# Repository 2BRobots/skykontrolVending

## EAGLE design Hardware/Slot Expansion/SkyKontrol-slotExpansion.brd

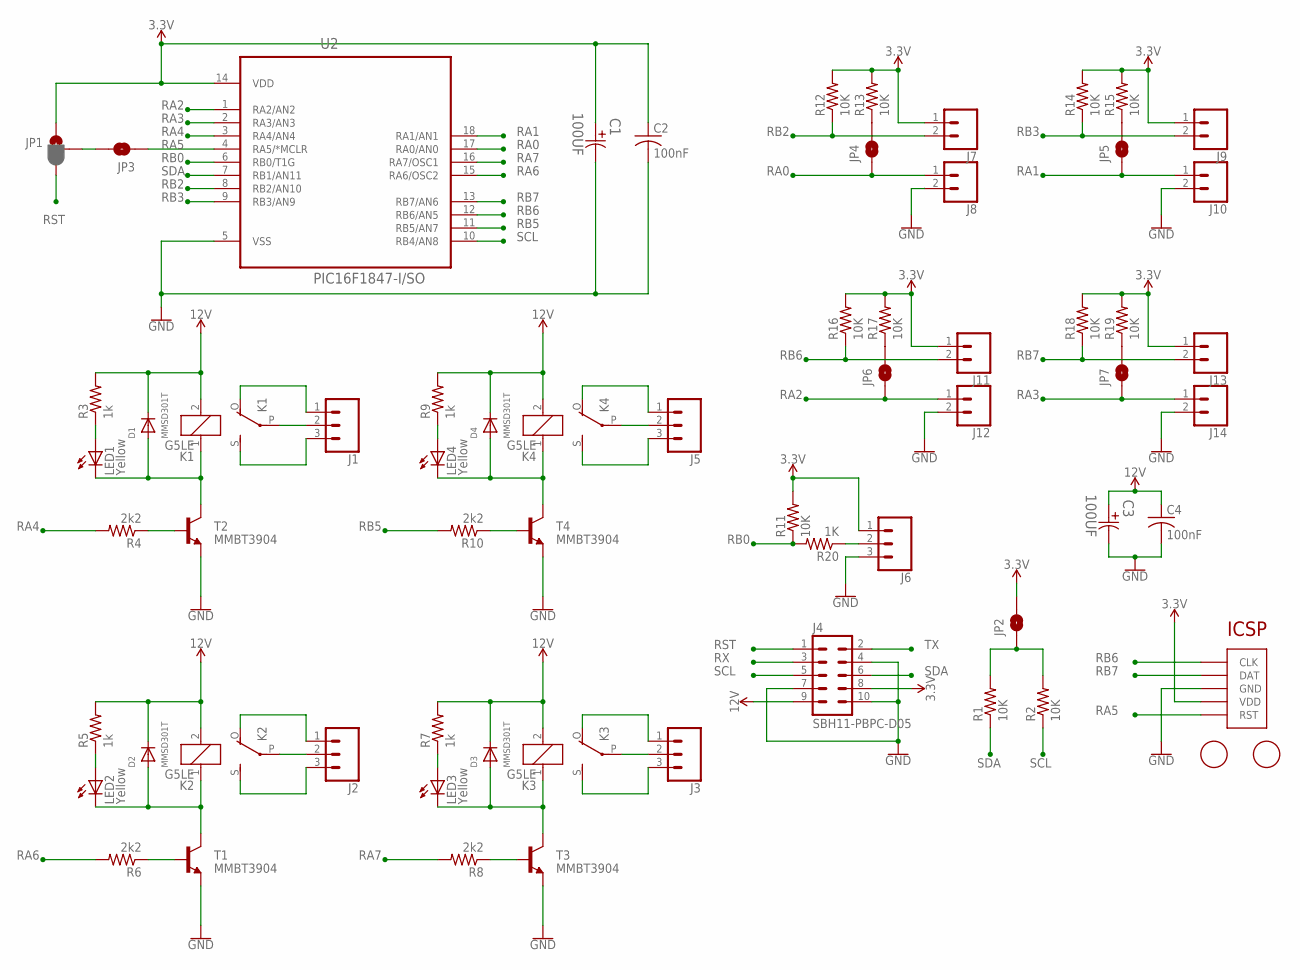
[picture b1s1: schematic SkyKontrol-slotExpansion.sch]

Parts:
C1, C3: 100UF; CAPAE660X800N
C2, C4: 100nF; C0603K
D1, D2, D3, D4: MMSD301T; SOD-123
J1, J2, J3, J5, J6: CONN_03-SCREW-5MM; SCREWTERMINAL-5MM-3
J4: SBH11-PBPC-D05
J7, J8, J9, J10, J11, J12, J13, J14: CONN_025MM; SCREWTERMINAL-5MM-2
JP1: JUMPER-SMT_3_1-NC_PASTE_SILK; SMT-JUMPER_3_1-NC_PASTE_SILK
JP2, JP3, JP4, JP5, JP6, JP7: JUMPER-SMT_2_NO_SILK; SMT-JUMPER_2_NO_SILK
K1, K2, K3, K4: G5LE
LED1, LED2, LED3, LED4: Yellow; CHIPLED_1206
R1, R2, R11, R12, R13, R14, R15, R16, R17, R18, R19: 10K; R0805
R3, R5, R7, R9: 1k; R0805
R4, R6, R8, R10: 2k2; R0805
R20: 1K; R0805
T1, T2, T3, T4: MMBT3904; SOT23-BEC
U2: PIC16F1847-I/SO; SOIC127P1030X265-18N
U$1, U$3: FIDUCIAL; FIDUCIAL_1MM
U$2: ICSP_POGO

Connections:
3.3V: C1.1, C2.1, J4.8, J6.1, J7.1, J9.1, J11.1, J13.1, JP1.1, JP2.2, R11.2, R12.2, R13.2, R14.2, R15.2, R16.2, R17.2, R18.2, R19.2, U2.14 (VDD), U$2.P$2 (VDD)
12V: C3.1, C4.1, D1.C, D2.C, D3.C, D4.C, J4.9, K1.2, K2.2, K3.2, K4.2, R3.2, R5.2, R7.2, R9.2
GND: C1.2, C2.2, C3.2, C4.2, J4.4, J4.7, J4.10, J6.3, J8.2, J10.2, J12.2, J14.2, T1.E, T2.E, T3.E, T4.E, U2.5 (VSS), U$2.P$3 (GND)
unnamed: JP1.2, JP3.2
unnamed: J1.2, K1.P
unnamed: J1.3, K1.S
unnamed: J1.1, K1.O
unnamed: JP2.1, R1.2, R2.2
unnamed: D1.A, K1.1, LED1.C, T2.C
unnamed: J2.2, K2.P
unnamed: J2.3, K2.S
unnamed: LED1.A, R3.1
unnamed: R4.1, T2.B
unnamed: J6.2, R20.1
unnamed: J2.1, K2.O
unnamed: D2.A, K2.1, LED2.C, T1.C
unnamed: LED2.A, R5.1
unnamed: R6.1, T1.B
unnamed: J3.2, K3.P
unnamed: J3.3, K3.S
unnamed: J3.1, K3.O
unnamed: D3.A, K3.1, LED3.C, T3.C
unnamed: LED3.A, R7.1
unnamed: R8.1, T3.B
unnamed: J5.2, K4.P
unnamed: J5.3, K4.S
unnamed: J5.1, K4.O
unnamed: D4.A, K4.1, LED4.C, T4.C
unnamed: LED4.A, R9.1
unnamed: R10.1, T4.B
unnamed: JP4.2, R13.1
unnamed: JP5.2, R15.1
unnamed: JP6.2, R17.1
unnamed: JP7.2, R19.1
RA0: J8.1, JP4.1, U2.17 (RA0/AN0)
RA1: J10.1, JP5.1, U2.18 (RA1/AN1)
RA2: J12.1, JP6.1, U2.1 (RA2/AN2)
RA3: J14.1, JP7.1, U2.2 (RA3/AN3)
RA4: R4.2, U2.3 (RA4/AN4)
RA5: JP3.1, U2.4 (RA5/*MCLR), U$2.P$1 (RST)
RA6: R6.2, U2.15 (RA6/OSC2)
RA7: R8.2, U2.16 (RA7/OSC1)
RB0: R11.1, R20.2, U2.6 (RB0/T1G)
RB2: J7.2, R12.1, U2.8 (RB2/AN10)
RB3: J9.2, R14.1, U2.9 (RB3/AN9)
RB5: R10.2, U2.11 (RB5/AN7)
RB6: J11.2, R16.1, U2.12 (RB6/AN5), U$2.P$5 (CLK)
RB7: J13.2, R18.1, U2.13 (RB7/AN6), U$2.P$4 (DAT)
RST: J4.1, JP1.3
RX: J4.3
SCL: J4.5, R2.1, U2.10 (RB4/AN8)
SDA: J4.6, R1.1, U2.7 (RB1/AN11)
TX: J4.2

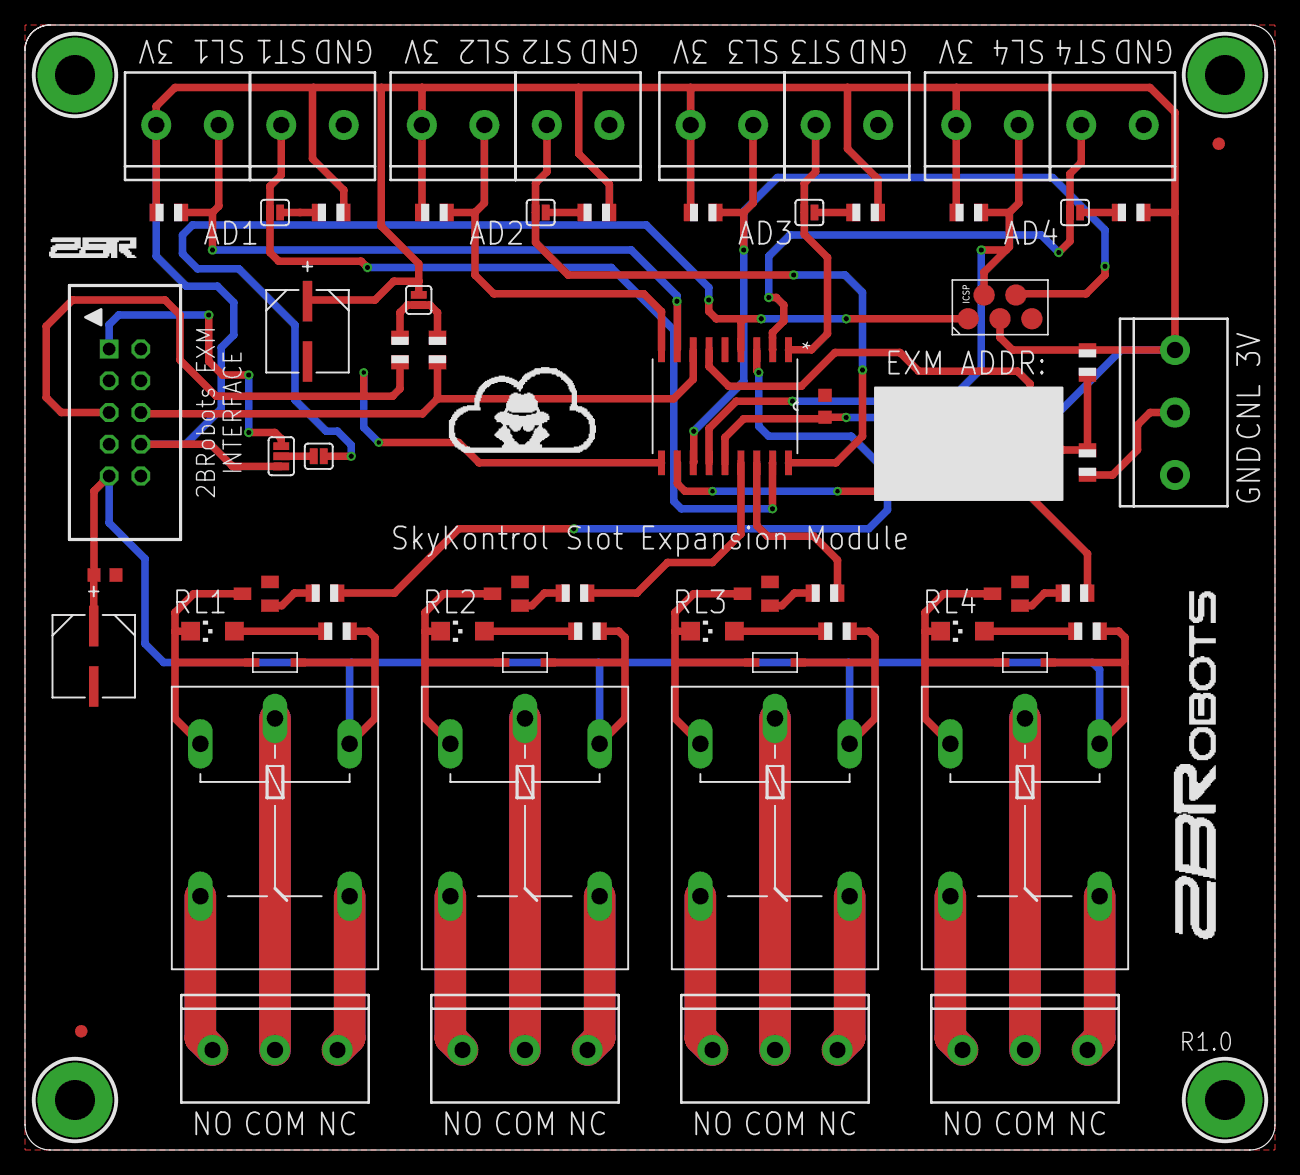
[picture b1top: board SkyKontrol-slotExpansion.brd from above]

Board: 2 copper layers, 100.0 x 90.0 mm, 65 parts (0 on the bottom side), 51 nets.

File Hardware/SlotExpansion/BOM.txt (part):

Part Value                        Device                       Package                      Description                                                                                                     MF MPN             OC_FARNELL OC_NEWARK PACKAGE PIC POGO POPULARITY PROD_ID    PROGRAMING SF_SKU    SMT SUPPLIER  TOLERANCE VALUE VOLTAGERATING
C1   100UF                        EEE-HA1E101XP-CASE-D8        CAPAE660X800N                Aluminum Electrolytic Capacitors,Surface Mount Type                                                                EEE-HA1E101XP   1973328    58T9236   CASE-D8                                                         PANASONIC ±20 %     100UF 25V          
C2   100nF                        C-USC0603K                   C0603K                       CAPACITOR, American symbol                                                                                                                                                                                                                                     
C3   100UF                        EEE-HA1E101XP-CASE-D8        CAPAE660X800N                Aluminum Electrolytic Capacitors,Surface Mount Type                                                                EEE-HA1E101XP   1973328    58T9236   CASE-D8                                                         PANASONIC ±20 %     100UF 25V          
C4   100nF                        C-USC0603K                   C0603K                       CAPACITOR, American symbol                                                                                                                                                                                                                                     
D1   MMSD301T                     DIODESOD-123                 SOD-123                      Diode                                                                                                                                                                                                                                                          
D2   MMSD301T                     DIODESOD-123                 SOD-123                      Diode                                                                                                                                                                                                                                                          
D3   MMSD301T                     DIODESOD-123                 SOD-123                      Diode                                                                                                                                                                                                                                                          
D4   MMSD301T                     DIODESOD-123                 SOD-123                      Diode                                                                                                                                                                                                                                                          
J1                                CONN_03-SCREW-5MM            SCREWTERMINAL-5MM-3          Multi connection point. Often used as Generic Header-pin footprint for 0.1 inch spaced/style header connections                                                                     CONN-10134            PRT-08433                                            
J2                                CONN_03-SCREW-5MM            SCREWTERMINAL-5MM-3          Multi connection point. Often used as Generic Header-pin footprint for 0.1 inch spaced/style header connections                                                                     CONN-10134            PRT-08433                                            
J3                                CONN_03-SCREW-5MM            SCREWTERMINAL-5MM-3          Multi connection point. Often used as Generic Header-pin footprint for 0.1 inch spaced/style header connections                                                                     CONN-10134            PRT-08433                                            
J4   SBH11-PBPC-D05               SBH11-PBPC-D05               SBH11-PBPC-D05               HEADER - Vertical, Shrouded                                                                                                                                                                                                                                    
J5                                CONN_03-SCREW-5MM            SCREWTERMINAL-5MM-3          Multi connection point. Often used as Generic Header-pin footprint for 0.1 inch spaced/style header connections                                                                     CONN-10134            PRT-08433                                            
J6                                CONN_03-SCREW-5MM            SCREWTERMINAL-5MM-3          Multi connection point. Often used as Generic Header-pin footprint for 0.1 inch spaced/style header connections                                                                     CONN-10134            PRT-08433                                            
J7                                CONN_025MM                   SCREWTERMINAL-5MM-2          Multi connection point. Often used as Generic Header-pin footprint for 0.1 inch spaced/style header connections                                                                                           PRT-08432                                            
J8                                CONN_025MM                   SCREWTERMINAL-5MM-2          Multi connection point. Often used as Generic Header-pin footprint for 0.1 inch spaced/style header connections                                                                                           PRT-08432                                            
J9                                CONN_025MM                   SCREWTERMINAL-5MM-2          Multi connection point. Often used as Generic Header-pin footprint for 0.1 inch spaced/style header connections                                                                                           PRT-08432                                            
J10                               CONN_025MM                   SCREWTERMINAL-5MM-2          Multi connection point. Often used as Generic Header-pin footprint for 0.1 inch spaced/style header connections                                                                                           PRT-08432                                            
J11                               CONN_025MM                   SCREWTERMINAL-5MM-2          Multi connection point. Often used as Generic Header-pin footprint for 0.1 inch spaced/style header connections                                                                                           PRT-08432                                            
J12                               CONN_025MM                   SCREWTERMINAL-5MM-2          Multi connection point. Often used as Generic Header-pin footprint for 0.1 inch spaced/style header connections                                                                                           PRT-08432                                            
J13                               CONN_025MM                   SCREWTERMINAL-5MM-2          Multi connection point. Often used as Generic Header-pin footprint for 0.1 inch spaced/style header connections                                                                                           PRT-08432                                            
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

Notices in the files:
parts and their libraries:
con-sullins: Copyright (C) 2009, Bob Starr
SparkFun-Jumpers: Licensing: Creative Commons ShareAlike 4.0 International - https://creativecommons.org/licenses/by-sa/4.0
